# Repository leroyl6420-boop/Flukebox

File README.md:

# Flukebox
A portable, off-grid, open-source MP3 player! Supports Bluetooth Classic and analog headphones. 

# Overview
The Flukebox V1.0 is yet another MP3 player for the Hack Clubber who is sick of tired of paying for Spotify Premium. With its ESP32-WROOM-32E-N8 and PCM5102 DAC module, the Flukebox can be used with either Bluetooth or wired analog headphones. With the recommended 8GB Micro SD card, it can hold more than 50 hours of 320 kbps of MP3 music. The 1100 mah battery keeps the Flukebox running for up to 7 hours, and its TP4056 charger supporting USB-C will have a full charge in as little as 90 minutes. Best of all, the Flukebox gives you all that performance in a 90x60 mm case that is only 20mm thick.

# PCB Design

The Flukebox V1.0 uses a two-layer PCB to house all its MCU's, modules, resistors and capacitors. Due to my inexperience in soldering, I didn't feel ready to order a bunch of bare components off Digikey or LCSC and solder them all together. Instead, I ordered modules for the things I needed the Flukebox to do, and am planning to solder them right onto the PCB using cut pin headers or solid wire. I will probably ditch this strategy in a future version, but it'll do for now. At least it makes the schematic and PCB design easier.

# CAD

The CAD for the Flukebox was pretty simple. I gave the PCB a 0.2 mm clearance on both sides, made a case, cut some holes for the USB-C charger and the analog headphone jack, made a lid, cut holes for the OLED, buttons, power switch, and EC11, and that was pretty much it. I have a lot of experience in these things. What was more fun was making an assembly of the finished PCB using KiCad's STEP model and models of the components I'm using I found online. I think it looks super cool! It's just a shame how the pads for the ESP-WROOM-32 didn't render, forcing me to take measurements from KiCad. Oh, well.

# BOM

Here are all the components you'll need for the Flukebox V1.0:

| Part | Quantity | Cost | Link |
|---|---:|---:|---|
| Flukebox V1.0 PCB | 1 | $6.14 | [PCBWay](https://www.pcbway.com/) |
| 1100mAh 3.7V LiPo Battery | 1 | $6.15 | [Amazon](https://www.amazon.com/EEMB-1100mAh-Battery-Rechargeable-Connector/dp/B08VRYS8FT) |
| Micro SD Reader | 1 | $5.99 | [Amazon](https://www.amazon.com/Adapter-Reader-Interface-Arduino-Raspberry/dp/B0H493ZTBM) |
| 128x64 OLED | 1 | $3.00 | [Amazon](https://www.amazon.com/Hosyond-Display-Self-Luminous-Compatible-Raspberry/dp/B09T6SJBV5) |
| TP4056 Charging Module | 1 | $5.99 | [Amazon](https://www.amazon.com/HiLetgo-Lithium-Charging-Protection-Functions/dp/B07PKND8KG) |
| EC11 Rotary Encoder | 1 | $3.00 | [Amazon](https://www.amazon.com/WWZMDiB-Encoder-Digital-Potentiometer-Arduino/dp/B0C6Q67V97) |
| 6x6mm 4-pin Push Buttons | 3 | $0.15 | [Amazon](https://www.amazon.com/QTEATAK-Momentary-Tactile-Button-Switch/dp/B07VSNN9S2) |
| PCM5102 DAC Module | 1 | $8.88 | [Amazon](https://www.amazon.com/PCM5102-PCM5102A-Digital-Converter-Raspberry/dp/B0DNW32Y46) |
| ESPRESSIF ESP32-WROOM-32E-N8 | 1 | $5.43 | [DigiKey](https://www.digikey.com/en/products/detail/espressif-systems/ESP32-WROOM-32E-N8/13159522) |
| Slide Switch | 1 | $0.30 | [Amazon](https://www.amazon.com/Position-Breadboard-Electronic-Miniature-SlideSwitch/dp/B09R3XLVVS) |
| MCP1826S-3302E/AB | 1 | $1.32 | [DigiKey](https://www.digikey.com/en/products/detail/microchip-technology/MCP1826S-3302E-AB/1635996) |
| 0.1uF / 100nF Capacitor | 1 | $0.07 | [Amazon](https://www.amazon.com/Cermant-Ceramic-Capacitor-Electronic-Components/dp/B09XV2H8JQ) |
| 1uF 5x11 Capacitor | 1 | $0.40 | [Amazon](https://www.amazon.com/ALLECIN-Electrolytic-Capacitor-0-2x0-43in-Capacitors/dp/B0CMQC587X) |
| 10uF 5x11 Capacitor | 1 | $0.40 | [Amazon](https://www.amazon.com/ALLECIN-Electrolytic-Capacitor-0-2x0-43in-Capacitors/dp/B0CMQ8FNQL) |
| 10kΩ Resistors | 2 | $0.12 | [Amazon](https://www.amazon.com/EDGELEC-Resistor-Tolerance-Multiple-Resistance/dp/B07QJB31M7) |
| 8GB Micro SD Card *(recommended)* | 1 | $19.99 | [Amazon](https://www.amazon.com/Sandisk-Flash-Memory-Card-SDSDQM-008G-B35/dp/B001D0ROGO) |
| **Total** |  | **$67.33** | |

Of course, you'll also need lead, a soldering iron, and a 3D printer w/filament to print the case and the lid out. Those prices will vary. However, when you don't count those miscellaneous prices, the Flukebox V1.0 will run you $67.33, pre-taxes! That's pretty good!

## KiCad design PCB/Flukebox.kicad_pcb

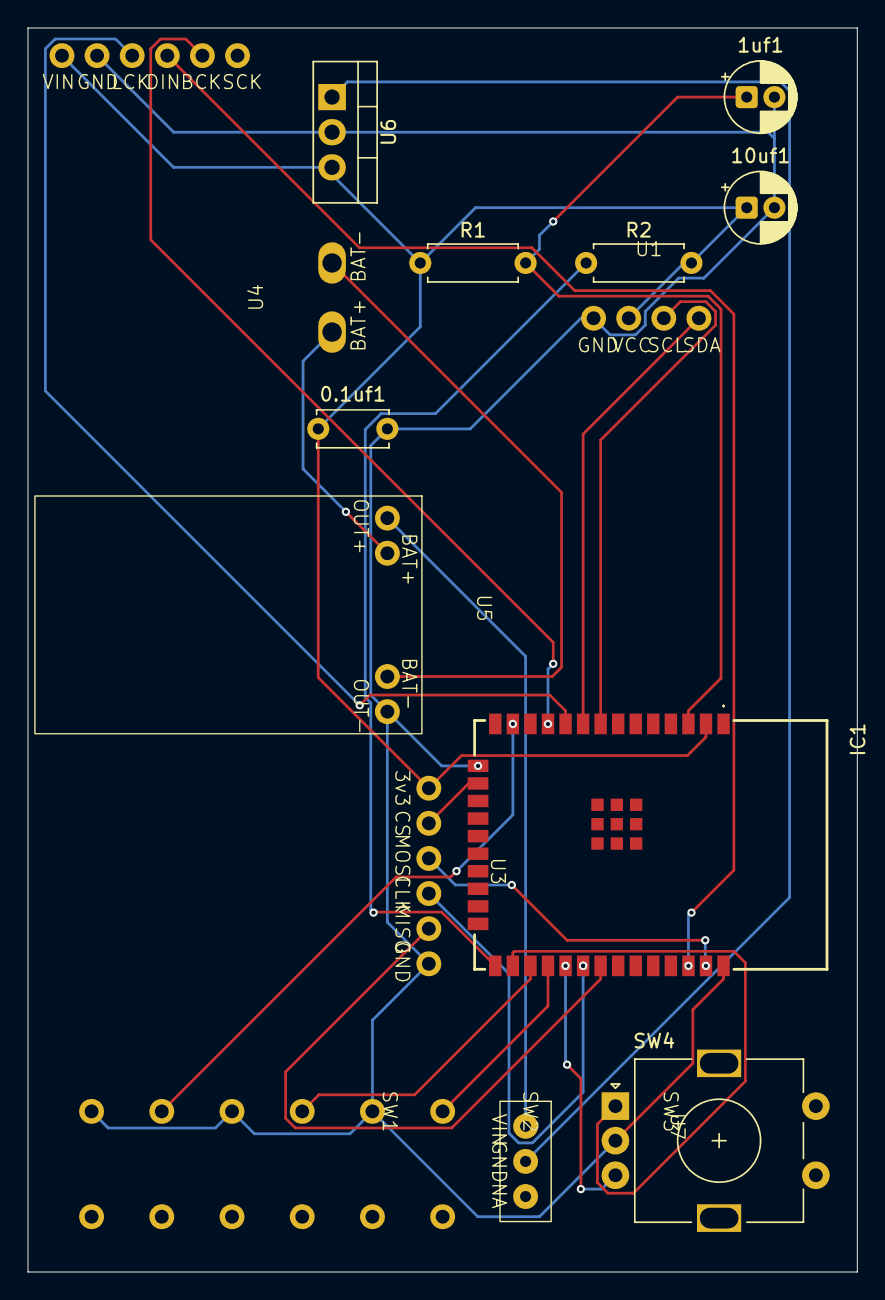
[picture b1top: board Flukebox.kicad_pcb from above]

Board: 2 copper layers, 60.0 x 90.0 mm, 17 parts (0 on the bottom side), 23 nets.

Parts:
0.1uf1: C_Polarized; C_Disc_D5.0mm_W2.5mm_P5.00mm
1uf1, 10uf1: C_Polarized; CP_Radial_D5.0mm_P2.00mm
IC1: ESP32-WROOM-32E-N8; ESP32WROOM32EN8
R1, R2: R_US; R_Axial_DIN0207_L6.3mm_D2.5mm_P7.62mm_Horizontal
SW1, SW2, SW3: SW_Push_Dual; Push_Button_4pin
SW4: RotaryEncoder; RotaryEncoder_Alps_EC11E-Switch_Vertical_H20mm
U1: 128x64_OLED_4pin
U2: DAC_Module_6pin
U3: Micro_SD_Reader_6pin
U4: Spliced_Lipo_Battery
U5: TP4056_Charging_Module_4pin
U6: MCP1826S; TO-220-3_Vertical
U7: Slide_Switch_3pin

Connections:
unnamed: 0.1uf1.1, 10uf1.1, IC1.2 (3V3), R1.1, R2.2, U1.2 (VCC), U2.1 (VIN), U3.1 (3v3), U6.3 (VO)
unnamed: 1uf1.1, IC1.3 (EN), R1.2
unnamed: IC1.25 (IO0), R2.1
unnamed: IC1.26 (IO4), SW4.A
unnamed: IC1.29 (IO5), SW4.B
unnamed: IC1.16 (IO13), U3.2 (CS)
unnamed: IC1.13 (IO14), SW1.1
unnamed: IC1.27 (IO16), SW2.1
unnamed: IC1.28 (IO17), SW3.1
unnamed: IC1.30 (IO18), U3.4 (CLK)
unnamed: IC1.31 (IO19), U3.5 (MISO)
unnamed: IC1.36 (IO22), U2.4 (DIN)
unnamed: IC1.37 (IO23), U3.3 (MOSI)
unnamed: IC1.10 (IO25), U2.3 (LCK)
unnamed: IC1.11 (IO26), U2.5 (BCK)
unnamed: IC1.8 (IO32), U1.3 (SCL)
unnamed: IC1.9 (IO33), U1.4 (SDA)
unnamed: IC1.17 (NC), IC1.18 (NC), IC1.19 (NC), IC1.20 (NC), IC1.21 (NC), IC1.22 (NC), IC1.32 (NC)
unnamed: 0.1uf1.2, 1uf1.2, 10uf1.2, IC1.1 (GND), IC1.15 (GND), IC1.38 (GND), IC1.39 (GND), IC1.40 (GND), IC1.41 (GND), IC1.42 (GND), IC1.43 (GND), IC1.44 (GND), IC1.45 (GND), IC1.46 (GND), IC1.47 (GND), SW1.3, SW2.3, SW3.3, SW4.C, U1.1 (GND), U2.2 (GND), U3.6 (GND), U5.4 (OUT-), U6.2 (GND)
unnamed: U4.1 (BAT+), U5.2 (BAT+)
unnamed: U4.2 (BAT-), U5.3 (BAT-)
unnamed: U5.1 (OUT+), U7.1 (VIN)
unnamed: U6.1 (VI), U7.2 (GND)
